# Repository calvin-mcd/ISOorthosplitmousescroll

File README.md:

# ISOorthosplitmousescroll
 An ortho board with ISO enter, rotary & both Cirque and Pimoroni support for mouse control

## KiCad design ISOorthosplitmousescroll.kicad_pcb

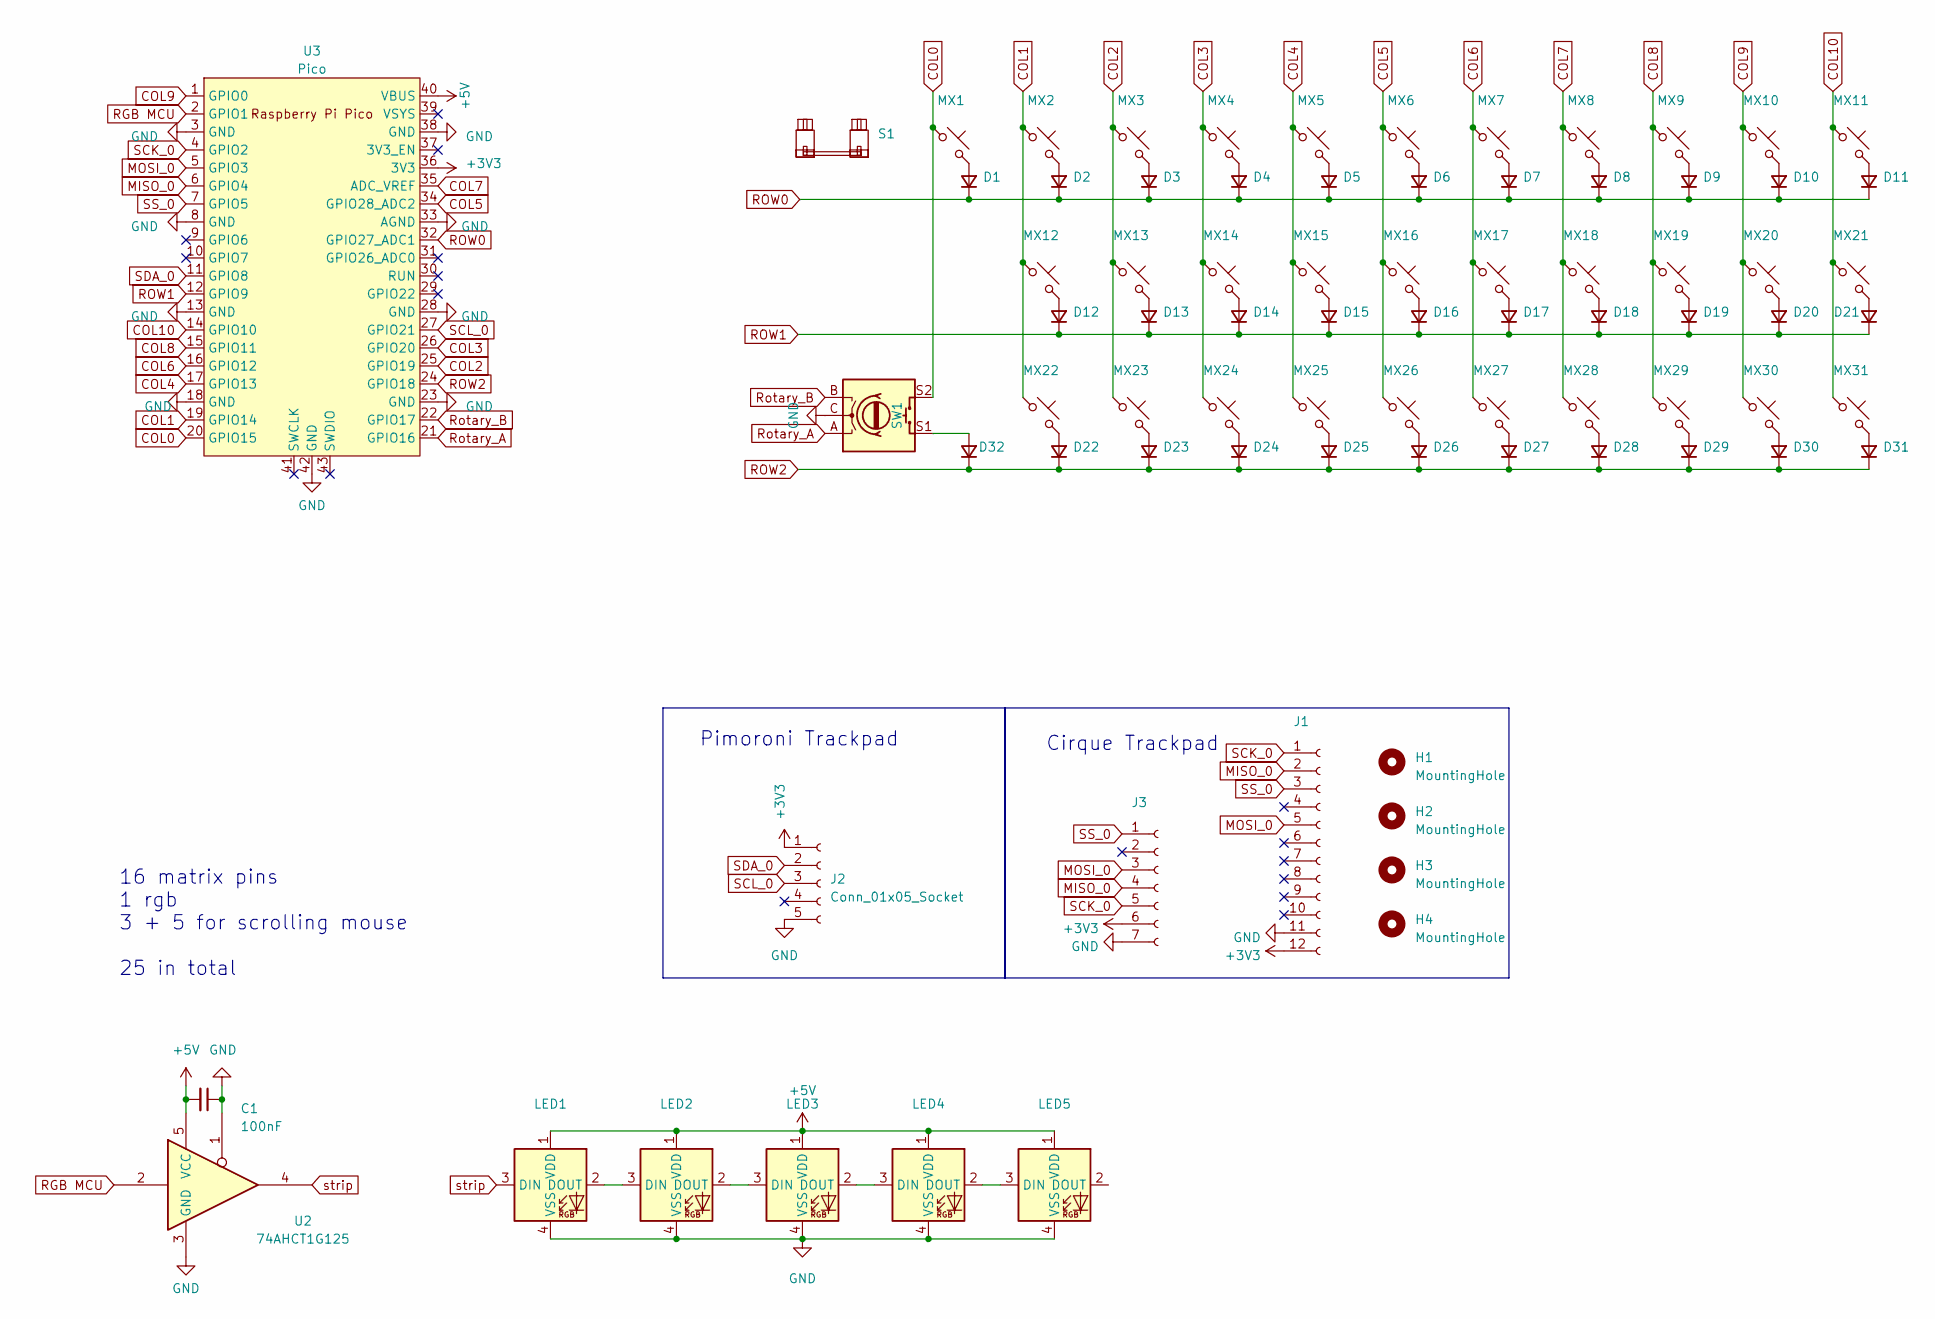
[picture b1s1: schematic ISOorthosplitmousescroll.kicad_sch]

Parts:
C1: 100nF; C_0805_2012Metric_Pad1.18x1.45mm_HandSolder
D1, D2, D3, D4, D5, D6, D7, D8, D9, D10, D11, D12, D13, D14, D15, D16, D17, D18, D19, D20, D21, D22, D23, D24, D25, D26, D27, D28, D29, D30, D31, D32: D_Small; Diode-Hybrid-Back
H1, H2, H3, H4: MountingHole; MountingHole_2.2mm_M2
J1: Conn_01x12_Female; vik-cirque-connector-horizontal
J2: Conn_01x05_Socket; pimoroni_trackball Mount Holes
J3: Conn_01x07_Socket; PinHeader_1x07_P2.54mm_Vertical
LED1, LED2, LED3, LED4, LED5: SK6812MINI-E; LED_6028R
MX1, MX2, MX3, MX4, MX5, MX6, MX7, MX8, MX9, MX10, MX11, MX12, MX13, MX14, MX15, MX16, MX17, MX18, MX19, MX20, MX21, MX22, MX23, MX24, MX25, MX26, MX27, MX28, MX29, MX30, MX31: MX_SW_solder; SW_MX_1u
S1: MX_stab; STAB_MX_ISO-ROT
SW1: RotaryEncoder_Switch; RotaryEncoder_EC11
U2: 74AHCT1G125; TSOT-23-5_HandSoldering
U3: Pico; RPi_Pico_SMD_TH

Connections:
+3V3: J1.12, J2.1, J3.6, U3.36 (3V3)
+5V: C1.2, LED1.1 (VDD), LED2.1 (VDD), LED3.1 (VDD), LED4.1 (VDD), LED5.1 (VDD), U2.5 (VCC), U3.40 (VBUS)
COL0: MX1.1, SW1.S2, U3.20 (GPIO15)
COL1: MX2.1, MX12.1, MX22.1, U3.19 (GPIO14)
COL2: MX3.1, MX13.1, MX23.1, U3.25 (GPIO19)
COL3: MX4.1, MX14.1, MX24.1, U3.26 (GPIO20)
COL4: MX5.1, MX15.1, MX25.1, U3.17 (GPIO13)
COL5: MX6.1, MX16.1, MX26.1, U3.34 (GPIO28_ADC2)
COL6: MX7.1, MX17.1, MX27.1, U3.16 (GPIO12)
COL7: MX8.1, MX18.1, MX28.1, U3.35 (ADC_VREF)
COL8: MX9.1, MX19.1, MX29.1, U3.15 (GPIO11)
COL9: MX10.1, MX20.1, MX30.1, U3.1 (GPIO0)
COL10: MX11.1, MX21.1, MX31.1, U3.14 (GPIO10)
GND: C1.1, J1.11, J2.5, J3.7, LED1.4 (VSS), LED2.4 (VSS), LED3.4 (VSS), LED4.4 (VSS), LED5.4 (VSS), SW1.C, U2.1, U2.3 (GND), U3.3 (GND), U3.8 (GND), U3.13 (GND), U3.18 (GND), U3.23 (GND), U3.28 (GND), U3.33 (AGND), U3.38 (GND), U3.42 (GND)
MISO_0: J1.2, J3.4, U3.6 (GPIO4)
MOSI_0: J1.5, J3.3, U3.5 (GPIO3)
unnamed: D1.2 (A), MX1.2
unnamed: D2.2 (A), MX2.2
unnamed: D3.2 (A), MX3.2
unnamed: D4.2 (A), MX4.2
unnamed: D5.2 (A), MX5.2
unnamed: D6.2 (A), MX6.2
unnamed: D7.2 (A), MX7.2
unnamed: D8.2 (A), MX8.2
unnamed: D9.2 (A), MX9.2
unnamed: D10.2 (A), MX10.2
unnamed: D11.2 (A), MX11.2
unnamed: D12.2 (A), MX12.2
unnamed: D13.2 (A), MX13.2
unnamed: D14.2 (A), MX14.2
unnamed: D15.2 (A), MX15.2
unnamed: D16.2 (A), MX16.2
unnamed: D17.2 (A), MX17.2
unnamed: D18.2 (A), MX18.2
unnamed: D19.2 (A), MX19.2
unnamed: D20.2 (A), MX20.2
unnamed: D21.2 (A), MX21.2
unnamed: D22.2 (A), MX22.2
unnamed: D23.2 (A), MX23.2
unnamed: D24.2 (A), MX24.2
unnamed: D25.2 (A), MX25.2
unnamed: D26.2 (A), MX26.2
unnamed: D27.2 (A), MX27.2
unnamed: D28.2 (A), MX28.2
unnamed: D29.2 (A), MX29.2
unnamed: D30.2 (A), MX30.2
unnamed: D31.2 (A), MX31.2
unnamed: D32.2 (A), SW1.S1
unnamed: LED1.2 (DOUT), LED2.3 (DIN)
unnamed: LED2.2 (DOUT), LED3.3 (DIN)
unnamed: LED3.2 (DOUT), LED4.3 (DIN)
unnamed: LED4.2 (DOUT), LED5.3 (DIN)
RGB MCU: U2.2, U3.2 (GPIO1)
ROW0: D1.1 (K), D2.1 (K), D3.1 (K), D4.1 (K), D5.1 (K), D6.1 (K), D7.1 (K), D8.1 (K), D9.1 (K), D10.1 (K), D11.1 (K), U3.32 (GPIO27_ADC1)
ROW1: D12.1 (K), D13.1 (K), D14.1 (K), D15.1 (K), D16.1 (K), D17.1 (K), D18.1 (K), D19.1 (K), D20.1 (K), D21.1 (K), U3.12 (GPIO9)
ROW2: D22.1 (K), D23.1 (K), D24.1 (K), D25.1 (K), D26.1 (K), D27.1 (K), D28.1 (K), D29.1 (K), D30.1 (K), D31.1 (K), D32.1 (K), U3.24 (GPIO18)
Rotary_A: SW1.A, U3.21 (GPIO16)
Rotary_B: SW1.B, U3.22 (GPIO17)
SCK_0: J1.1, J3.5, U3.4 (GPIO2)
SCL_0: J2.3, U3.27 (GPIO21)
SDA_0: J2.2, U3.11 (GPIO8)
SS_0: J1.3, J3.1, U3.7 (GPIO5)
strip: LED1.3 (DIN), U2.4

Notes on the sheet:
Cirque Trackpad
Pimoroni Trackpad
16 matrix pins 1 rgb 3 + 5 for scrolling mouse 25 in total

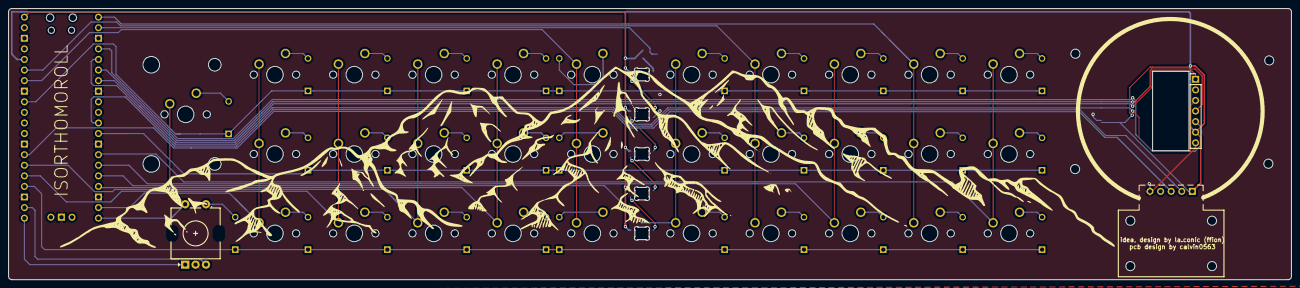
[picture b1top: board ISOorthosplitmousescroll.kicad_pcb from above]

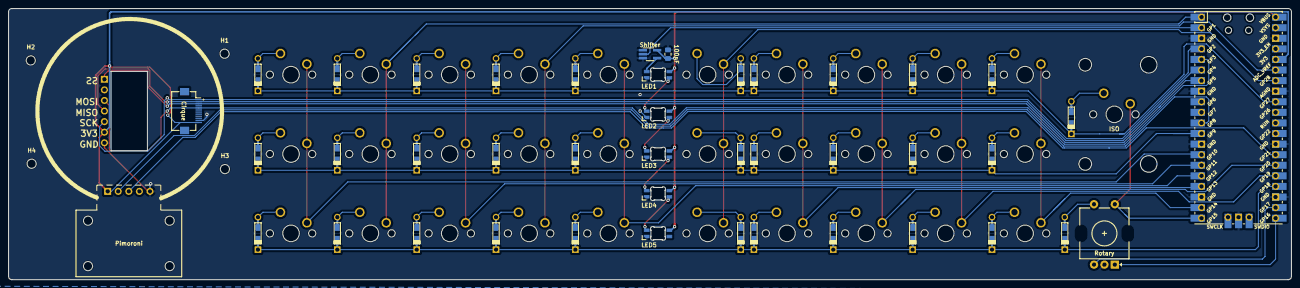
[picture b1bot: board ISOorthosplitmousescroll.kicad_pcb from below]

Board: 2 copper layers, 308.0 x 65.1 mm, 80 parts (9 on the bottom side), 63 nets.

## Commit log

2023-08-14 backup
2023-09-12 update project
